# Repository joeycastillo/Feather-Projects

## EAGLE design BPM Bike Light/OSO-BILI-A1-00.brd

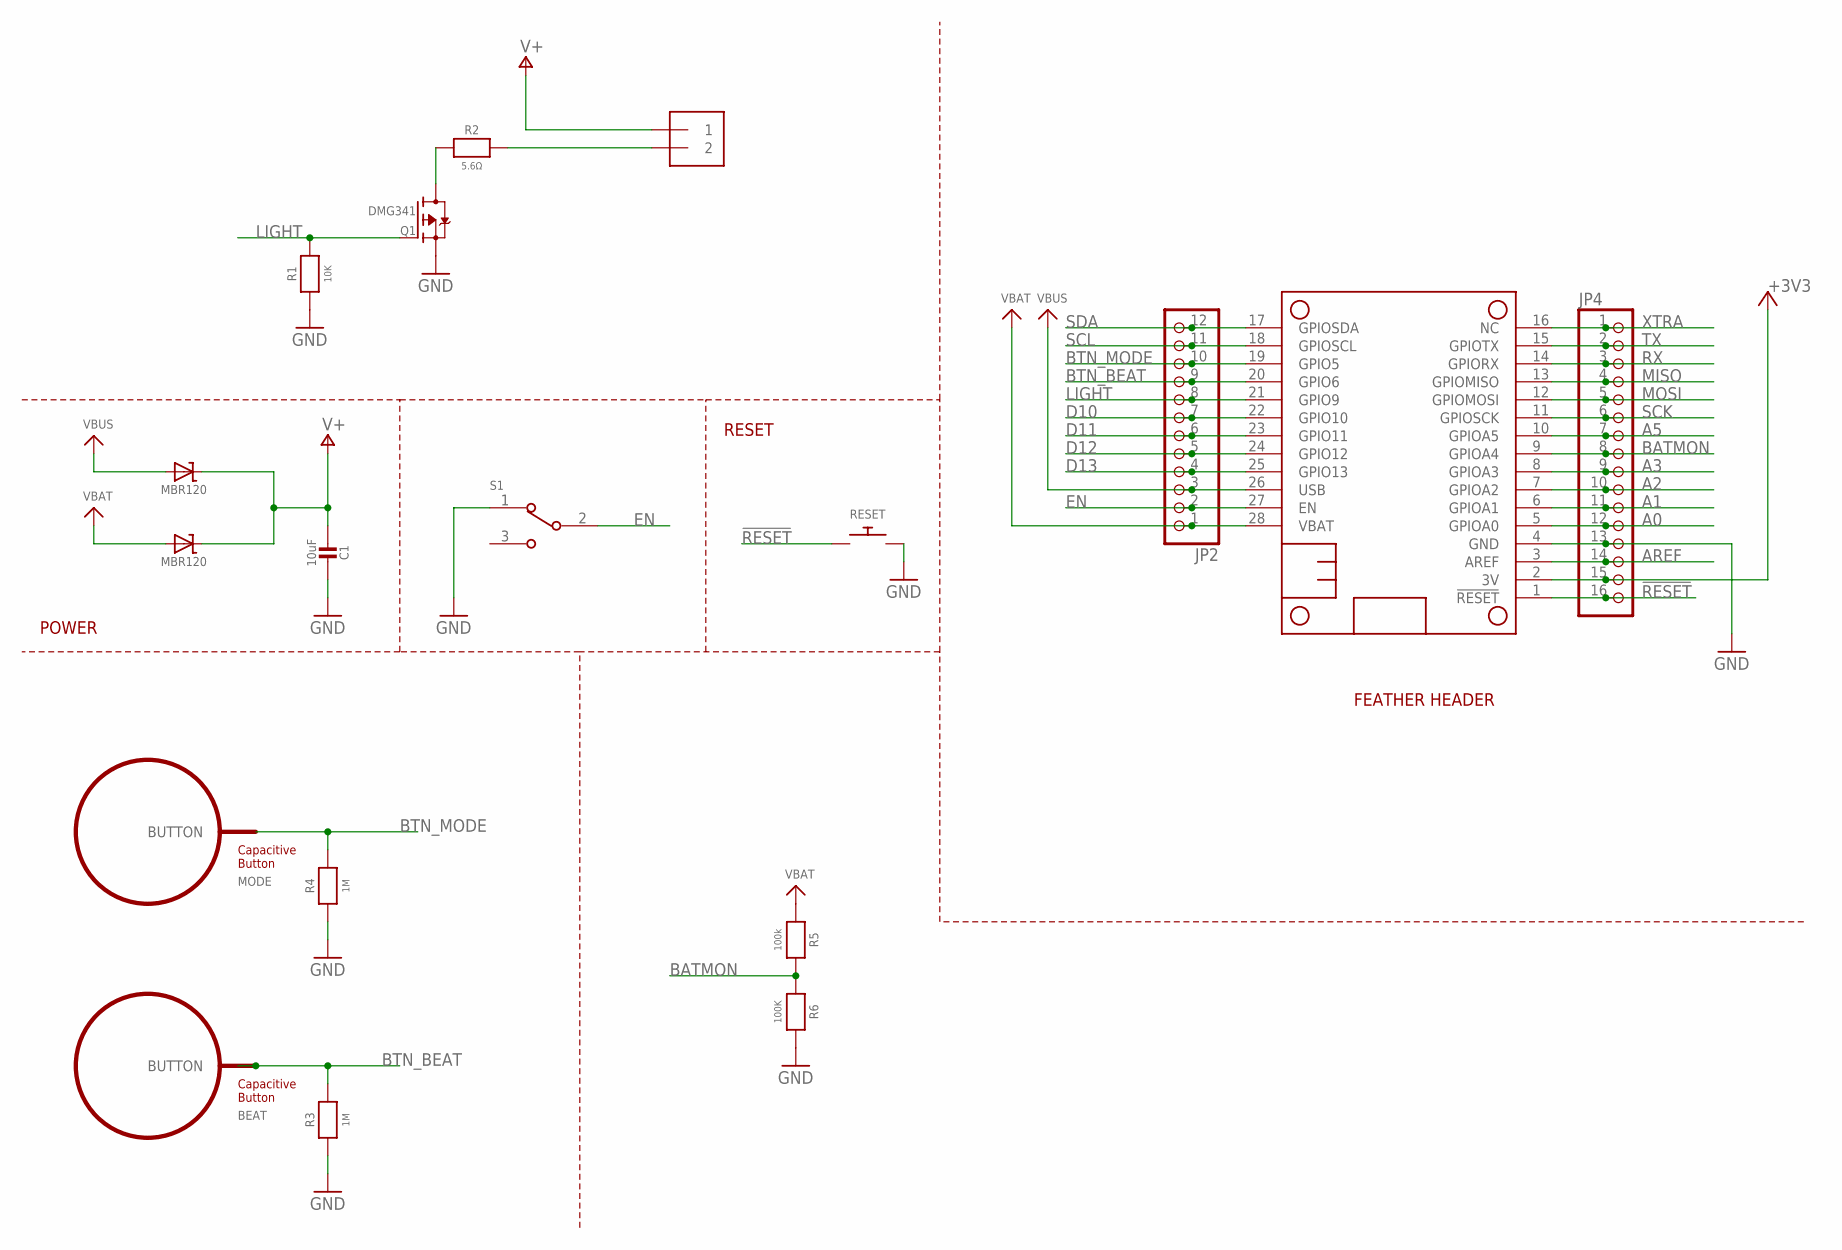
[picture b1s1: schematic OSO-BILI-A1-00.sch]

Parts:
BEAT: BUTTON_PASSIVE12MM; BUTTON_PASSIVE_12MM
C1: 10uF; 0805-NO
D1, D2: MBR120; SOD-123
J1: 1X25MM; 1X2-5MM
JP2: HEADER-1X12; 1X12_ROUND
JP4: HEADER-1X16ROUND; 1X16_ROUND
MODE: BUTTON_PASSIVE8MM; BUTTON_PASSIVE_8MM
MS1: FEATHERWING
Q1: DMG341; SOT23-R
R1: 10K; 0805-NO
R2: 5.6Ω; 2012
R3, R4: 1M; 0805-NO
R5: 100k; 0805_10MGAP
R6: 100K; 0805-NO
RESET: SWITCH_PUSHBUTTONC&K_KSS; BTN_CK_KSS
S1: JS102011SAQN; SW_JS102011SAQN

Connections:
3V: JP4.15, MS1.2 (3V)
!RESET: JP4.16, MS1.1 (!RESET), RESET.P$1
A0: JP4.12, MS1.5 (GPIOA0)
A1: JP4.11, MS1.6 (GPIOA1)
A2: JP4.10, MS1.7 (GPIOA2)
A3: JP4.9, MS1.8 (GPIOA3)
A5: JP4.7, MS1.10 (GPIOA5)
AREF: JP4.14, MS1.3 (AREF)
BATMON: JP4.8, MS1.9 (GPIOA4), R5.2, R6.1
BTN_BEAT: BEAT.BUTTON, JP2.9, MS1.20 (GPIO6), R3.2
BTN_MODE: JP2.10, MODE.BUTTON, MS1.19 (GPIO5), R4.2
D10: JP2.7, MS1.22 (GPIO10)
D11: JP2.6, MS1.23 (GPIO11)
D12: JP2.5, MS1.24 (GPIO12)
D13: JP2.4, MS1.25 (GPIO13)
EN: JP2.2, MS1.27 (EN), S1.2
GND: C1.1, JP4.13, MS1.4 (GND), Q1.2 (S), R1.1, R3.1, R4.1, R6.2, RESET.P$2, S1.1
LIGHT: JP2.8, MS1.21 (GPIO9), Q1.1 (G), R1.2
MISO: JP4.4, MS1.13 (GPIOMISO)
MOSI: JP4.5, MS1.12 (GPIOMOSI)
unnamed: Q1.3 (D), R2.1
unnamed: J1.2, R2.2
RX: JP4.3, MS1.14 (GPIORX)
SCK: JP4.6, MS1.11 (GPIOSCK)
SCL: JP2.11, MS1.18 (GPIOSCL)
SDA: JP2.12, MS1.17 (GPIOSDA)
TX: JP4.2, MS1.15 (GPIOTX)
V+: C1.2, D1.C, D2.C, J1.1
VBAT: D2.A, JP2.1, MS1.28 (VBAT), R5.1
VBUS: D1.A, JP2.3, MS1.26 (USB)
XTRA: JP4.1, MS1.16 (NC)

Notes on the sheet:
POWER
RESET
FEATHER HEADER

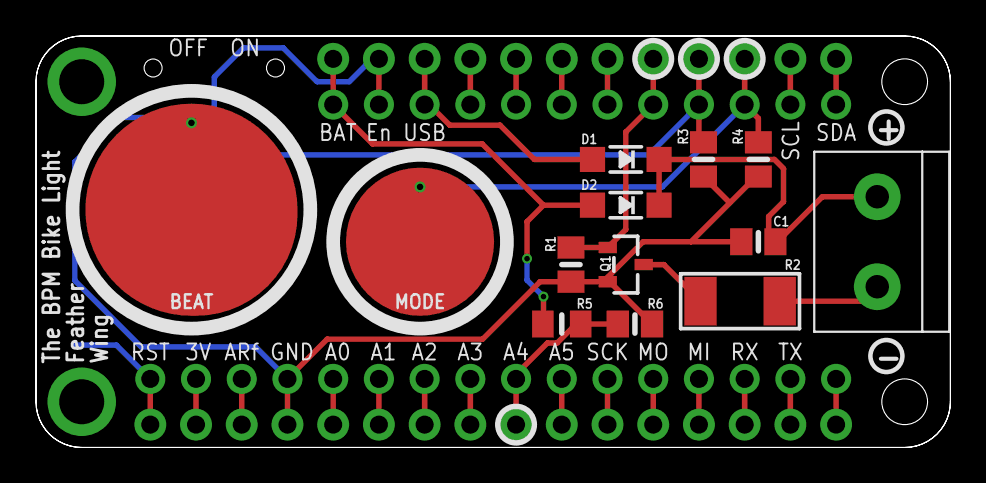
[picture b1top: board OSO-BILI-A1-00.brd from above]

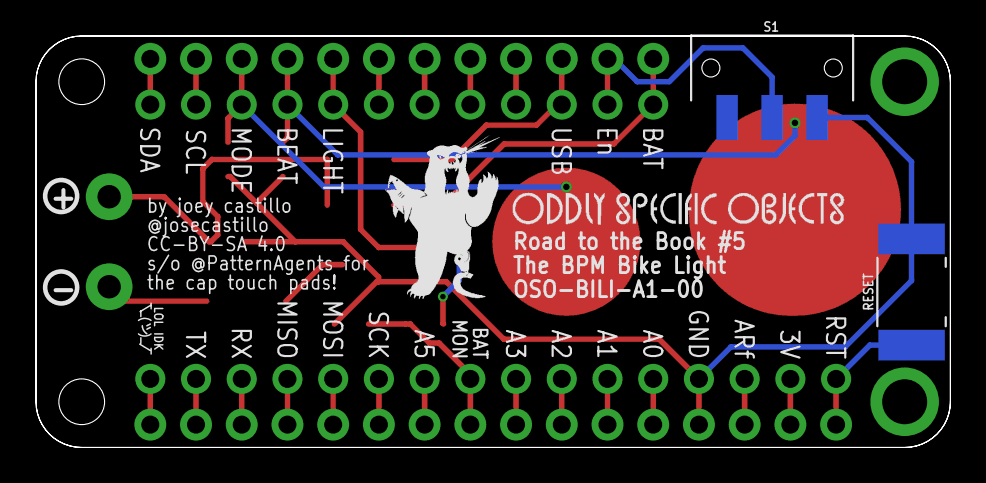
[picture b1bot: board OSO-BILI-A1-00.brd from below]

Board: 2 copper layers, 50.8 x 22.9 mm, 20 parts (4 on the bottom side), 31 nets.

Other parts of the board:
U$1: OSO_BEAR_250X360MIL_1000DPI
U$3: OSO_WORDMARK_ONELINE_725MIL_1000DPI

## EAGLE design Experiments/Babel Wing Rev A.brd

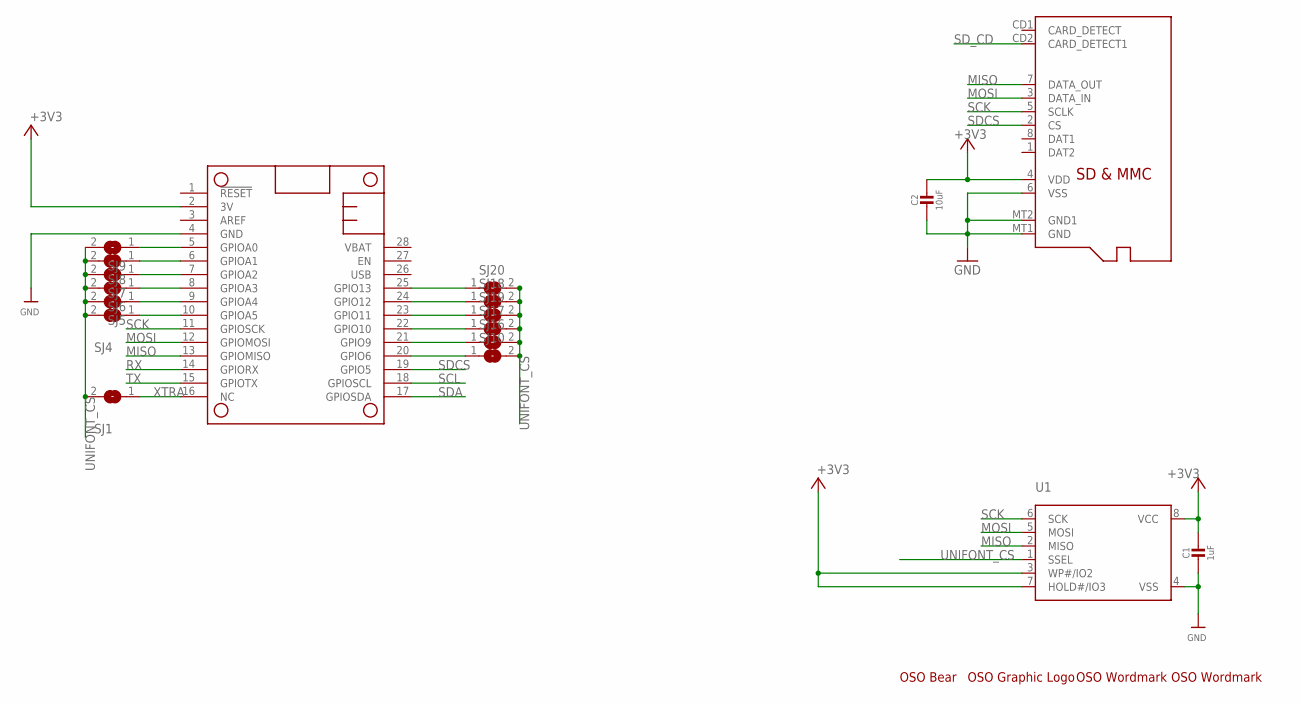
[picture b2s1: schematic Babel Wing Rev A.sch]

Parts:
C1: 1uF; 0805_10MGAP
C2: 10uF; 0805_10MGAP
MICROSD: MICROSD
MS1: FEATHERWING
SJ1, SJ4, SJ5, SJ6, SJ7, SJ8, SJ9, SJ10, SJ16, SJ17, SJ18, SJ19, SJ20: SOLDERJUMPER; SOLDERJUMPER_ARROW_NOPASTE
U1: MICROBUILDER_SPIFLASH_SOIC8; MICROBUILDER_SOIC8_150MIL
U$2: OSO_BEAR; OSO_BEAR_750MIL
U$3: OSO_GRAPHIC
U$4: OSO_TEXT; OSO_TEXT_435MIL
U$5: OSO_TEXTOSO_TEXT_ONELINE_125MIL; OSO_ONELINE_125MIL

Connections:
+3V3: C1.1, C2.1, MICROSD.4 (VDD), MS1.2 (3V), U1.3 (WP#/IO2), U1.7 (HOLD#/IO3), U1.8 (VCC)
GND: C1.2, C2.2, MICROSD.6 (VSS), MICROSD.MT1 (GND), MICROSD.MT2 (GND1), MS1.4 (GND), U1.4 (VSS)
MISO: MICROSD.7 (DATA_OUT), MS1.13 (GPIOMISO), U1.2 (MISO)
MOSI: MICROSD.3 (DATA_IN), MS1.12 (GPIOMOSI), U1.5 (MOSI)
unnamed: MS1.20 (GPIO6), SJ10.1
unnamed: MS1.10 (GPIOA5), SJ4.1
unnamed: MS1.9 (GPIOA4), SJ5.1
unnamed: MS1.8 (GPIOA3), SJ6.1
unnamed: MS1.7 (GPIOA2), SJ7.1
unnamed: MS1.6 (GPIOA1), SJ8.1
unnamed: MS1.5 (GPIOA0), SJ9.1
unnamed: MS1.25 (GPIO13), SJ20.1
unnamed: MS1.24 (GPIO12), SJ18.1
unnamed: MS1.23 (GPIO11), SJ19.1
unnamed: MS1.22 (GPIO10), SJ17.1
unnamed: MS1.21 (GPIO9), SJ16.1
RX: MS1.14 (GPIORX)
SCK: MICROSD.5 (SCLK), MS1.11 (GPIOSCK), U1.6 (SCK)
SCL: MS1.18 (GPIOSCL)
SDA: MS1.17 (GPIOSDA)
SDCS: MICROSD.2 (CS), MS1.19 (GPIO5)
SD_CD: MICROSD.CD2 (CARD_DETECT1)
TX: MS1.15 (GPIOTX)
UNIFONT_CS: SJ1.2, SJ4.2, SJ5.2, SJ6.2, SJ7.2, SJ8.2, SJ9.2, SJ10.2, SJ16.2, SJ17.2, SJ18.2, SJ19.2, SJ20.2, U1.1 (SSEL)
XTRA: MS1.16 (NC), SJ1.1

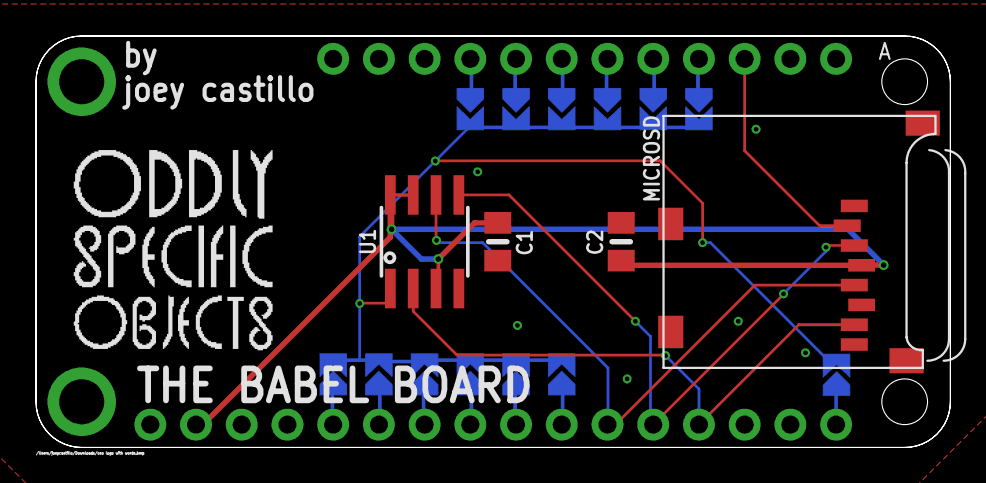
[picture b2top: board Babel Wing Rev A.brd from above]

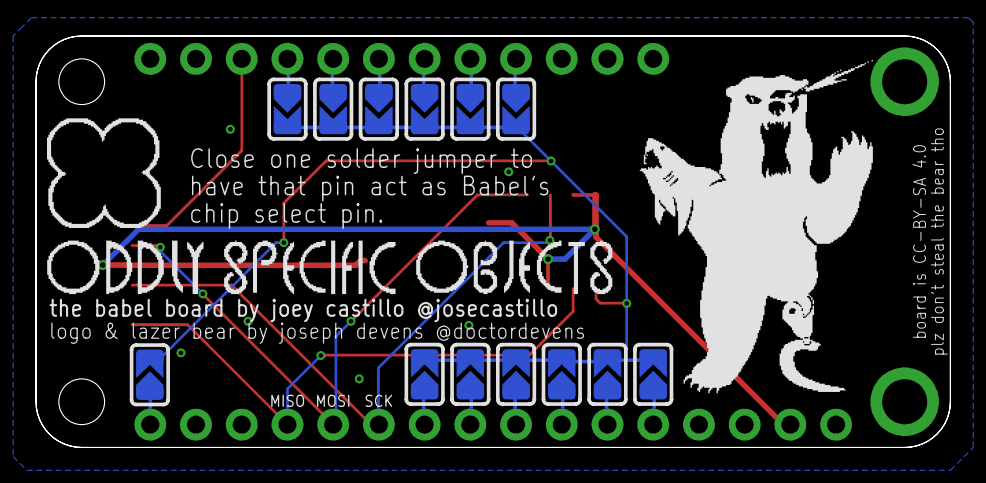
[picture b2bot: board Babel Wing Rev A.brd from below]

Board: 2 copper layers, 50.8 x 22.9 mm, 22 parts (16 on the bottom side), 20 nets.

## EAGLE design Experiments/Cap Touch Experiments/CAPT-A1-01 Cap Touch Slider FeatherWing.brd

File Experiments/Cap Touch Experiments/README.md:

# Capacitive Touch Experiments

Just some boards I made to play with the peripheral touch controller on the SAMD series boards. 

Slider design is based on a CC-licensed design from [Pattern Agents](http://www.patternagents.com/news/2013/11/29/touch-widgets-howto.html)

Matrix design kind of started from their passive matrix, but I expanded it and redid the symbol to work for my intended uses.

# Self-Capacitance Slider Wing

The slider wing should "just work" with [Adafruit FreeTouch](https://github.com/adafruit/Adafruit_FreeTouch) on the following boards:

* [Feather M0](https://www.adafruit.com/product/2772)
* [Feather M0 Express](https://www.adafruit.com/product/3403)
* [Feather M0 Adalogger](https://www.adafruit.com/product/2796)
* [Feather M0 Wifi](https://www.adafruit.com/product/3010)
* [Feather M0 Bluefruit LE](https://www.adafruit.com/product/2995)
* All the [LoRa](https://www.adafruit.com/product/3178) [and](https://www.adafruit.com/product/3179) [RadioFruit](https://www.adafruit.com/product/3176) [boards](https://www.adafruit.com/product/3177)

I'd love to get it working with the SAMD51-based [Feather M4 Express](https://www.adafruit.com/product/3857) but there's currently no open source support for the PTC on that board. If you want to hack on this, this slider might be an ideal testbed for that. (note that one of the segments is on a non-PTC line, so you would get a slightly shorter slider on the M4)

# Mutual Capacitance Matrix Shield

This board is kind of the opposite of "should just work". It's intended to work with the [Metro M0](https://www.adafruit.com/product/3505), but FreeTouch currently doesn't support mutual capacitance modes; I made this board so I could try hack on that. Also note that this shield kind of takes over almost all of your board's pins: it uses all of the analog pins and all but one of the digital pins, which isn't terribly convenient unless you're stacking with an SPI- or I2C-only shield.

If you're gonna try and play with this on a [Metro M4](https://www.adafruit.com/product/3382), that board lacks PTC functionality on pins A0 and A1, so I routed those pins to the top and bottom; this way, the matrix theoretically should work, just with a smaller touch area.

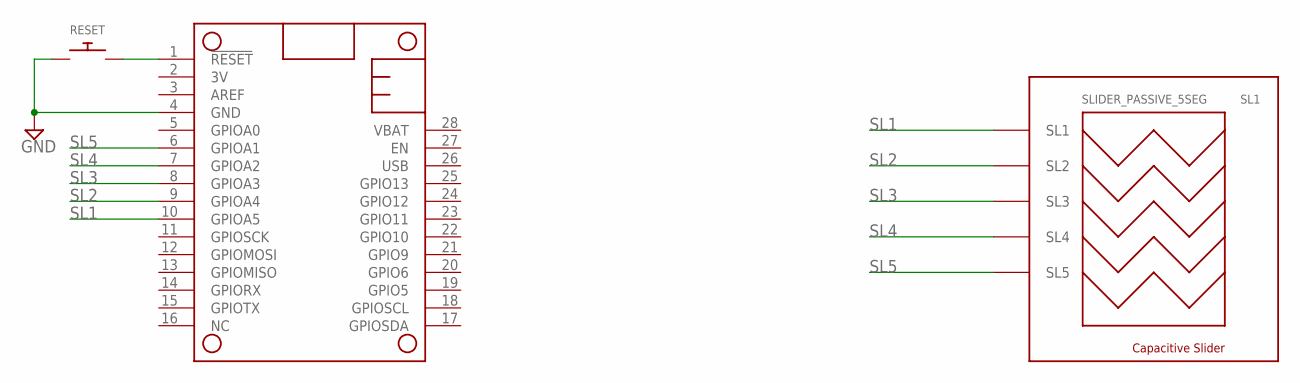
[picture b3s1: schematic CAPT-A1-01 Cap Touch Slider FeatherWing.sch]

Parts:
MS1: FEATHERWING
RESET: SPST_TACTILE_SWITCHRA-THRU; MJTP1117
SL1: SLIDER_PASSIVE_5SEG; SLIDER_PASSIVE_5SEG_12MM

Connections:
!RESET: MS1.1 (!RESET), RESET.P$2
GND: MS1.4 (GND), RESET.P$1
SL1: MS1.10 (GPIOA5), SL1.SL1
SL2: MS1.9 (GPIOA4), SL1.SL2
SL3: MS1.8 (GPIOA3), SL1.SL3
SL4: MS1.7 (GPIOA2), SL1.SL4
SL5: MS1.6 (GPIOA1), SL1.SL5

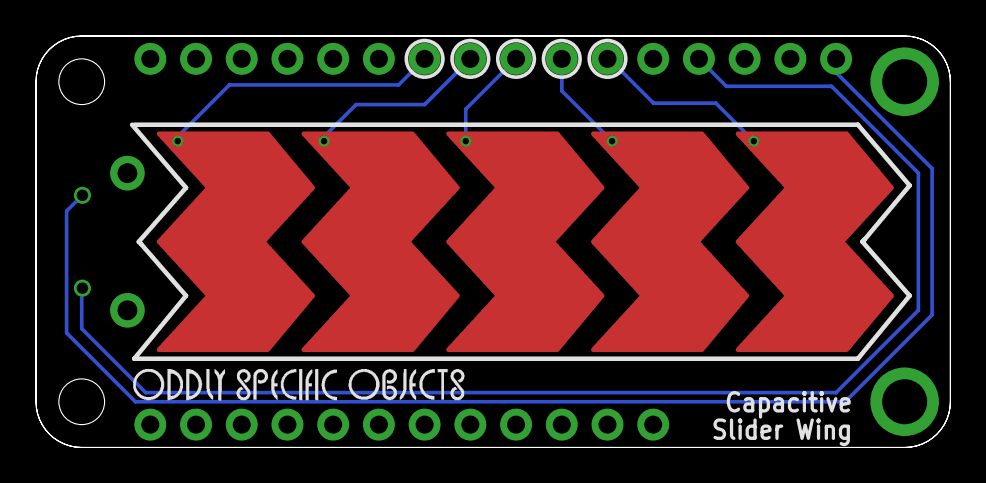
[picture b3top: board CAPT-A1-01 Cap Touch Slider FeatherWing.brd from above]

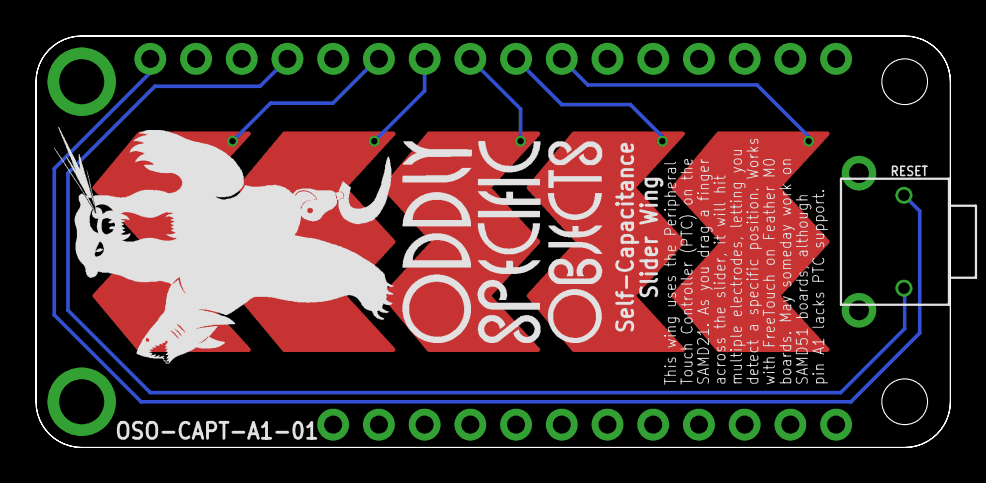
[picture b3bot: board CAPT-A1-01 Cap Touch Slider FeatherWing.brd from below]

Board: 2 copper layers, 50.8 x 22.9 mm, 6 parts (3 on the bottom side), 7 nets.

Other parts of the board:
U$1: OSO_WORDMARK_THREELINE_450MIL_1000DPI
U$2: OSO_BEAR_525X750MIL_1000DPI
U$3: OSO_WORDMARK_ONELINE_725MIL_1000DPI

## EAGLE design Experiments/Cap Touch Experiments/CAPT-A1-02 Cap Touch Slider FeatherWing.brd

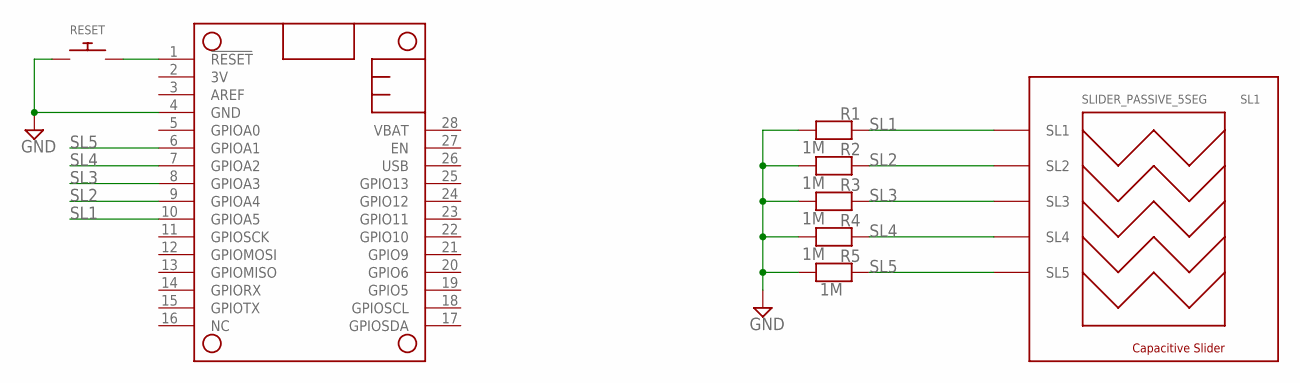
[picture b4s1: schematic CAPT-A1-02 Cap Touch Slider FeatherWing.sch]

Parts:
MS1: FEATHERWING
R1, R2, R3, R4, R5: 1M; 0805-NO
RESET: SPST_TACTILE_SWITCHRA-THRU; MJTP1117
SL1: SLIDER_PASSIVE_5SEG; SLIDER_PASSIVE_5SEG_12MM

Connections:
!RESET: MS1.1 (!RESET), RESET.P$2
GND: MS1.4 (GND), R1.2, R2.2, R3.2, R4.2, R5.2, RESET.P$1
SL1: MS1.10 (GPIOA5), R1.1, SL1.SL1
SL2: MS1.9 (GPIOA4), R2.1, SL1.SL2
SL3: MS1.8 (GPIOA3), R3.1, SL1.SL3
SL4: MS1.7 (GPIOA2), R4.1, SL1.SL4
SL5: MS1.6 (GPIOA1), R5.1, SL1.SL5

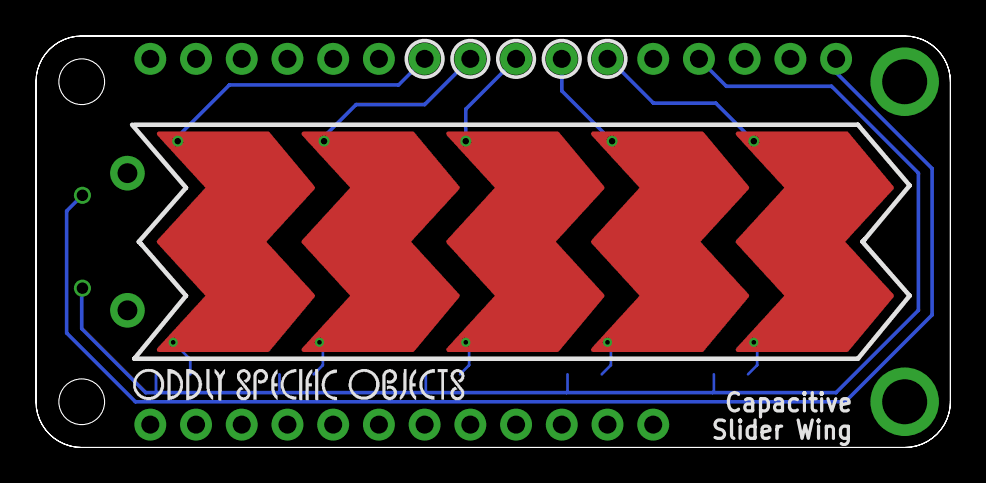
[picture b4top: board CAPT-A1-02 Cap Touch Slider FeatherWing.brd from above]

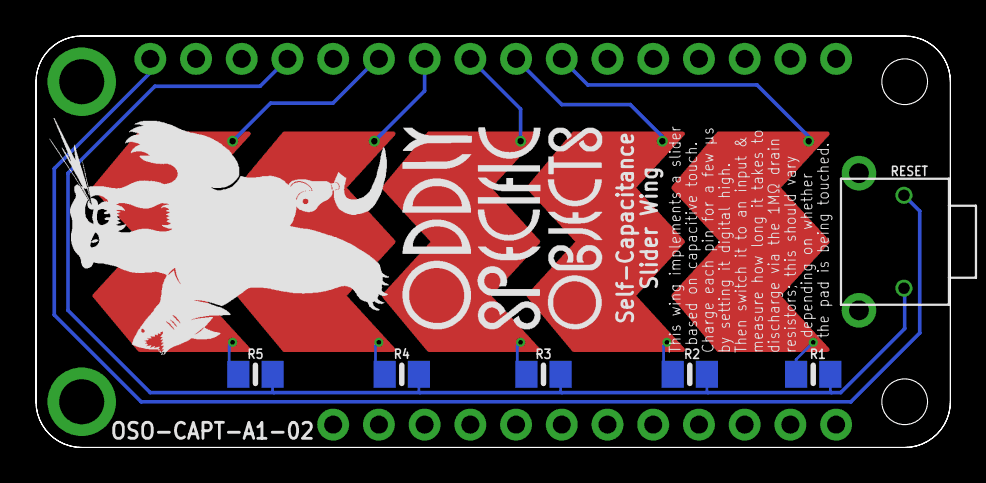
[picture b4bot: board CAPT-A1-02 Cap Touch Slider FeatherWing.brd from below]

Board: 2 copper layers, 50.8 x 22.9 mm, 11 parts (8 on the bottom side), 7 nets.

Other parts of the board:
U$1: OSO_WORDMARK_THREELINE_450MIL_1000DPI
U$2: OSO_BEAR_525X750MIL_1000DPI
U$3: OSO_WORDMARK_ONELINE_725MIL_1000DPI

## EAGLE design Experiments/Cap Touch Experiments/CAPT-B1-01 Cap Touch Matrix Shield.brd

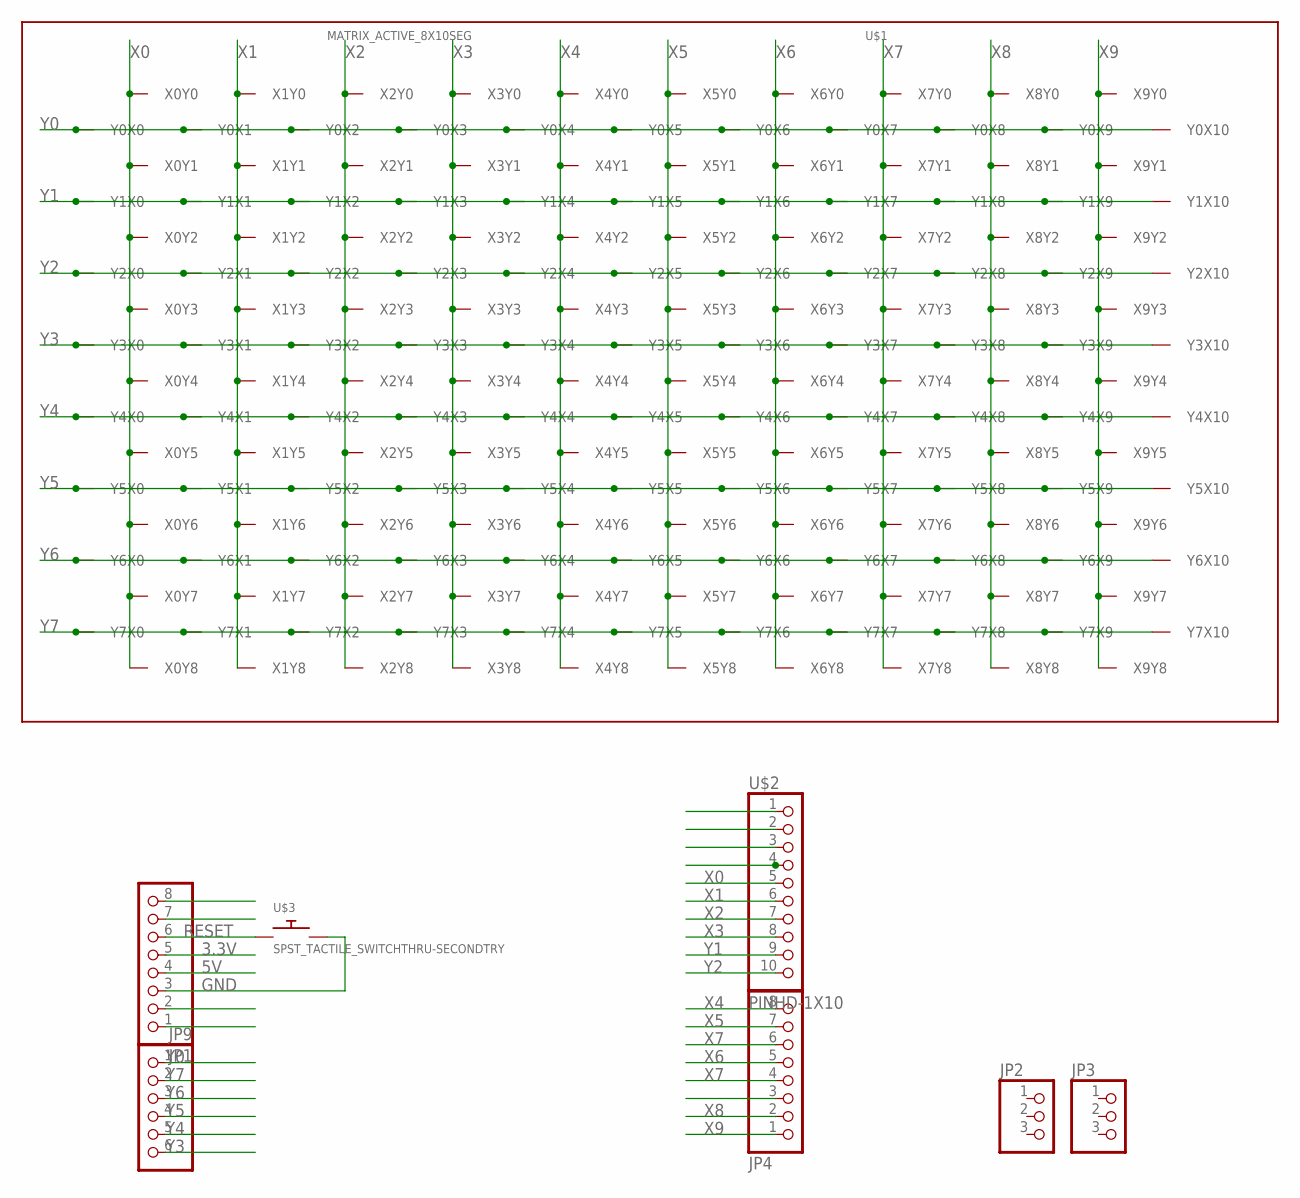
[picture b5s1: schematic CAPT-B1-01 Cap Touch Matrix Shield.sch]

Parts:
JP1, JP4: PINHD-1X8CLEANBIG; 1X08-CLEANBIG
JP2, JP3: PINHD-1X3CB; 1X03-CLEANBIG
JP9: PINHD-1X6CB; 1X06-CLEANBIG
U$1: MATRIX_ACTIVE_8X10SEG; MATRIX_ACTIVE_8X10SEG_4MM
U$2: PINHD-1X10; 1X10-BIG
U$3: SPST_TACTILE_SWITCHTHRU-SECONDTRY; MJTP1250-TRY2

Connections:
3.3V: JP1.5
5V: JP1.4
GND: JP1.3, U$3.P$2
RESET: JP1.6, U$3.P$1
X0: U$1.X0Y0, U$1.X0Y1, U$1.X0Y2, U$1.X0Y3, U$1.X0Y4, U$1.X0Y5, U$1.X0Y6, U$1.X0Y7, U$1.X0Y8, U$2.5
X1: U$1.X1Y0, U$1.X1Y1, U$1.X1Y2, U$1.X1Y3, U$1.X1Y4, U$1.X1Y5, U$1.X1Y6, U$1.X1Y7, U$1.X1Y8, U$2.6
X2: U$1.X2Y0, U$1.X2Y1, U$1.X2Y2, U$1.X2Y3, U$1.X2Y4, U$1.X2Y5, U$1.X2Y6, U$1.X2Y7, U$1.X2Y8, U$2.7
X3: U$1.X3Y0, U$1.X3Y1, U$1.X3Y2, U$1.X3Y3, U$1.X3Y4, U$1.X3Y5, U$1.X3Y6, U$1.X3Y7, U$1.X3Y8, U$2.8
X4: JP4.8, U$1.X4Y0, U$1.X4Y1, U$1.X4Y2, U$1.X4Y3, U$1.X4Y4, U$1.X4Y5, U$1.X4Y6, U$1.X4Y7, U$1.X4Y8
X5: JP4.7, U$1.X5Y0, U$1.X5Y1, U$1.X5Y2, U$1.X5Y3, U$1.X5Y4, U$1.X5Y5, U$1.X5Y6, U$1.X5Y7, U$1.X5Y8
X6: JP4.5, U$1.X6Y0, U$1.X6Y1, U$1.X6Y2, U$1.X6Y3, U$1.X6Y4, U$1.X6Y5, U$1.X6Y6, U$1.X6Y7, U$1.X6Y8
X7: JP4.4, JP4.6, U$1.X7Y0, U$1.X7Y1, U$1.X7Y2, U$1.X7Y3, U$1.X7Y4, U$1.X7Y5, U$1.X7Y6, U$1.X7Y7, U$1.X7Y8
X8: JP4.2, U$1.X8Y0, U$1.X8Y1, U$1.X8Y2, U$1.X8Y3, U$1.X8Y4, U$1.X8Y5, U$1.X8Y6, U$1.X8Y7, U$1.X8Y8
X9: JP4.1, U$1.X9Y0, U$1.X9Y1, U$1.X9Y2, U$1.X9Y3, U$1.X9Y4, U$1.X9Y5, U$1.X9Y6, U$1.X9Y7, U$1.X9Y8
Y0: JP9.1, U$1.Y0X0, U$1.Y0X1, U$1.Y0X2, U$1.Y0X3, U$1.Y0X4, U$1.Y0X5, U$1.Y0X6, U$1.Y0X7, U$1.Y0X8, U$1.Y0X9, U$1.Y0X10
Y1: U$1.Y1X0, U$1.Y1X1, U$1.Y1X2, U$1.Y1X3, U$1.Y1X4, U$1.Y1X5, U$1.Y1X6, U$1.Y1X7, U$1.Y1X8, U$1.Y1X9, U$1.Y1X10, U$2.9
Y2: U$1.Y2X0, U$1.Y2X1, U$1.Y2X2, U$1.Y2X3, U$1.Y2X4, U$1.Y2X5, U$1.Y2X6, U$1.Y2X7, U$1.Y2X8, U$1.Y2X9, U$1.Y2X10, U$2.10
Y3: JP9.6, U$1.Y3X0, U$1.Y3X1, U$1.Y3X2, U$1.Y3X3, U$1.Y3X4, U$1.Y3X5, U$1.Y3X6, U$1.Y3X7, U$1.Y3X8, U$1.Y3X9, U$1.Y3X10
Y4: JP9.5, U$1.Y4X0, U$1.Y4X1, U$1.Y4X2, U$1.Y4X3, U$1.Y4X4, U$1.Y4X5, U$1.Y4X6, U$1.Y4X7, U$1.Y4X8, U$1.Y4X9, U$1.Y4X10
Y5: JP9.4, U$1.Y5X0, U$1.Y5X1, U$1.Y5X2, U$1.Y5X3, U$1.Y5X4, U$1.Y5X5, U$1.Y5X6, U$1.Y5X7, U$1.Y5X8, U$1.Y5X9, U$1.Y5X10
Y6: JP9.3, U$1.Y6X0, U$1.Y6X1, U$1.Y6X2, U$1.Y6X3, U$1.Y6X4, U$1.Y6X5, U$1.Y6X6, U$1.Y6X7, U$1.Y6X8, U$1.Y6X9, U$1.Y6X10
Y7: JP9.2, U$1.Y7X0, U$1.Y7X1, U$1.Y7X2, U$1.Y7X3, U$1.Y7X4, U$1.Y7X5, U$1.Y7X6, U$1.Y7X7, U$1.Y7X8, U$1.Y7X9, U$1.Y7X10

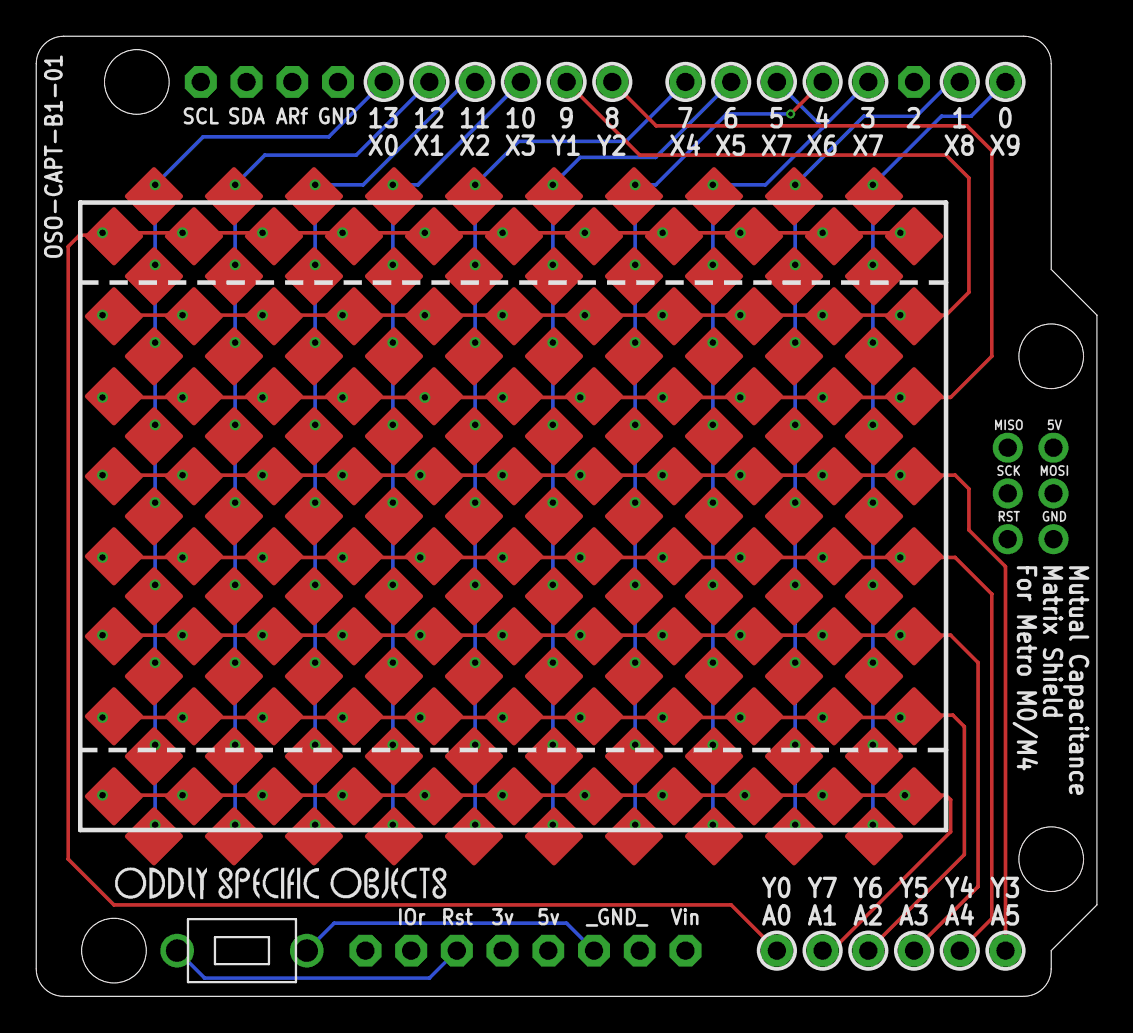
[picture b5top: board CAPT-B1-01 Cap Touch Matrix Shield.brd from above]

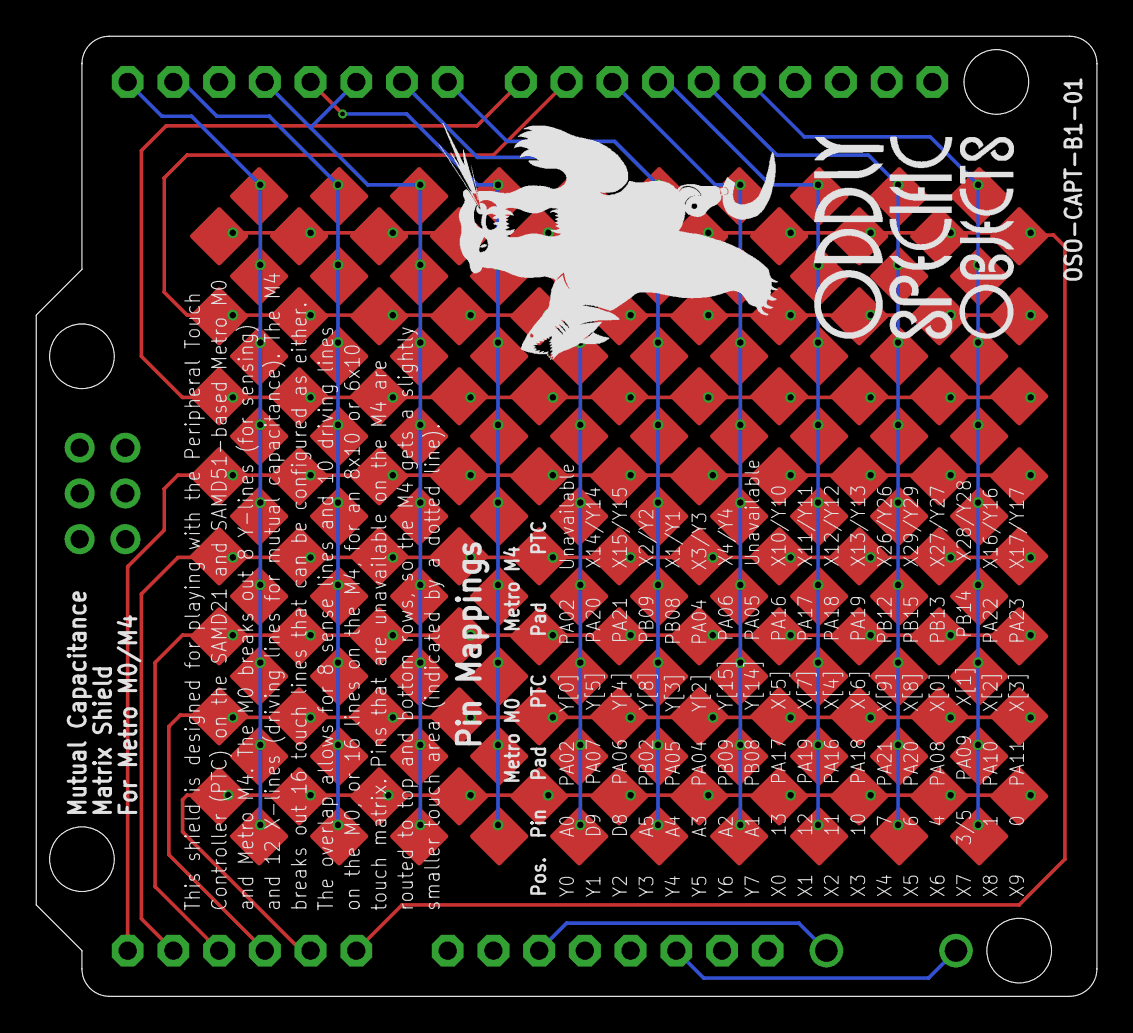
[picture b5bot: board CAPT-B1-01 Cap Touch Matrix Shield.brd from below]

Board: 2 copper layers, 58.9 x 53.3 mm, 11 parts (2 on the bottom side), 20 nets.

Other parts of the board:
U$4: OSO_BEAR_525X750MIL_1000DPI
U$5: OSO_WORDMARK_ONELINE_725MIL_1000DPI
U$6: OSO_WORDMARK_THREELINE_450MIL_1000DPI

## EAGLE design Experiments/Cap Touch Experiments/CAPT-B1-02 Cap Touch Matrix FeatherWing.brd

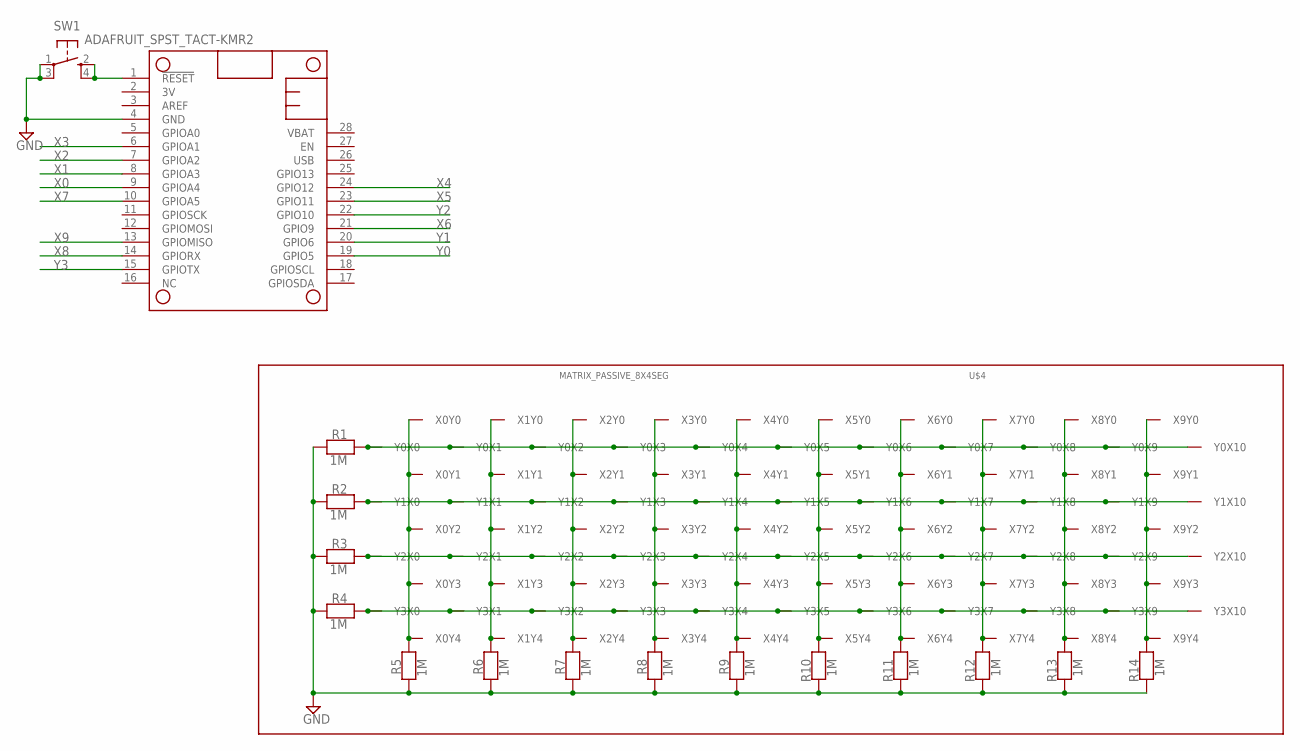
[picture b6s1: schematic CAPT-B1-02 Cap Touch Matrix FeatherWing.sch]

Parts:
MS2: MICROBUILDER_FEATHERWING_NOHOLES
R1, R2, R3, R4, R5, R6, R7, R8, R9, R10, R11, R12, R13, R14: 1M; 0805_10MGAP
SW1: ADAFRUIT_SPST_TACT-KMR2; ADAFRUIT_KMR2
U$4: MATRIX_PASSIVE_8X4SEG; MATRIX_ACTIVE_8X4SEG_4MM

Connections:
!RESET: MS2.1 (!RESET), SW1.2 (S), SW1.4 (S1)
GND: MS2.4 (GND), R1.2, R2.2, R3.2, R4.2, R5.2, R6.2, R7.2, R8.2, R9.2, R10.2, R11.2, R12.2, R13.2, R14.2, SW1.1, SW1.3 (P1)
X0: MS2.9 (GPIOA4), R5.1, U$4.X0Y0, U$4.X0Y1, U$4.X0Y2, U$4.X0Y3, U$4.X0Y4
X1: MS2.8 (GPIOA3), R6.1, U$4.X1Y0, U$4.X1Y1, U$4.X1Y2, U$4.X1Y3, U$4.X1Y4
X2: MS2.7 (GPIOA2), R7.1, U$4.X2Y0, U$4.X2Y1, U$4.X2Y2, U$4.X2Y3, U$4.X2Y4
X3: MS2.6 (GPIOA1), R8.1, U$4.X3Y0, U$4.X3Y1, U$4.X3Y2, U$4.X3Y3, U$4.X3Y4
X4: MS2.24 (GPIO12), R9.1, U$4.X4Y0, U$4.X4Y1, U$4.X4Y2, U$4.X4Y3, U$4.X4Y4
X5: MS2.23 (GPIO11), R10.1, U$4.X5Y0, U$4.X5Y1, U$4.X5Y2, U$4.X5Y3, U$4.X5Y4
X6: MS2.21 (GPIO9), R11.1, U$4.X6Y0, U$4.X6Y1, U$4.X6Y2, U$4.X6Y3, U$4.X6Y4
X7: MS2.10 (GPIOA5), R12.1, U$4.X7Y0, U$4.X7Y1, U$4.X7Y2, U$4.X7Y3, U$4.X7Y4
X8: MS2.14 (GPIORX), R13.1, U$4.X8Y0, U$4.X8Y1, U$4.X8Y2, U$4.X8Y3, U$4.X8Y4
X9: MS2.13 (GPIOMISO), R14.1, U$4.X9Y0, U$4.X9Y1, U$4.X9Y2, U$4.X9Y3, U$4.X9Y4
Y0: MS2.19 (GPIO5), R1.1, U$4.Y0X0, U$4.Y0X1, U$4.Y0X2, U$4.Y0X3, U$4.Y0X4, U$4.Y0X5, U$4.Y0X6, U$4.Y0X7, U$4.Y0X8, U$4.Y0X9, U$4.Y0X10
Y1: MS2.20 (GPIO6), R2.1, U$4.Y1X0, U$4.Y1X1, U$4.Y1X2, U$4.Y1X3, U$4.Y1X4, U$4.Y1X5, U$4.Y1X6, U$4.Y1X7, U$4.Y1X8, U$4.Y1X9, U$4.Y1X10
Y2: MS2.22 (GPIO10), R3.1, U$4.Y2X0, U$4.Y2X1, U$4.Y2X2, U$4.Y2X3, U$4.Y2X4, U$4.Y2X5, U$4.Y2X6, U$4.Y2X7, U$4.Y2X8, U$4.Y2X9, U$4.Y2X10
Y3: MS2.15 (GPIOTX), R4.1, U$4.Y3X0, U$4.Y3X1, U$4.Y3X2, U$4.Y3X3, U$4.Y3X4, U$4.Y3X5, U$4.Y3X6, U$4.Y3X7, U$4.Y3X8, U$4.Y3X9, U$4.Y3X10

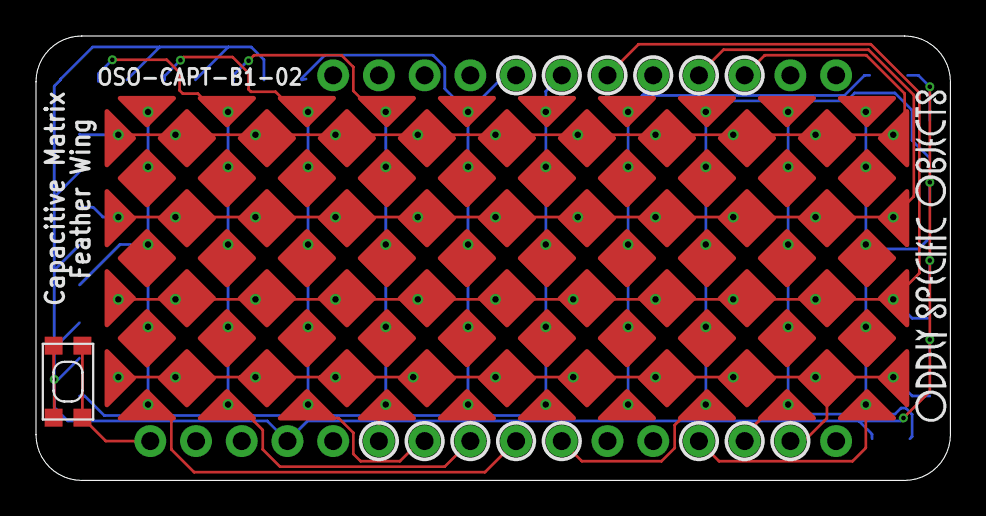
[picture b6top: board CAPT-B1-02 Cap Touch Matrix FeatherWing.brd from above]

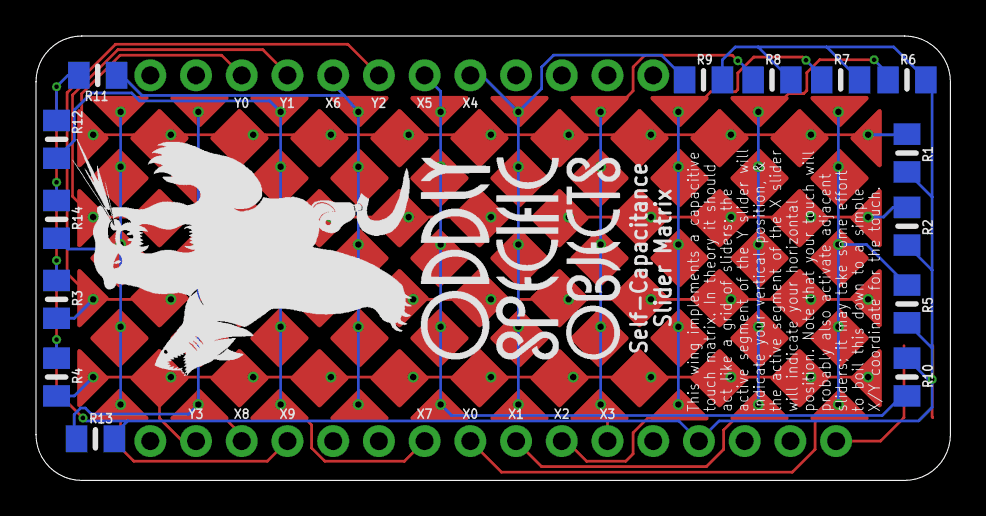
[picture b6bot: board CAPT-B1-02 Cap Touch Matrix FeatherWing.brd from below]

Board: 2 copper layers, 50.8 x 24.7 mm, 20 parts (16 on the bottom side), 16 nets.

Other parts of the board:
U$1: OSO_WORDMARK_THREELINE_450MIL_1000DPI
U$2: OSO_BEAR_525X750MIL_1000DPI
U$3: OSO_WORDMARK_ONELINE_725MIL_1000DPI

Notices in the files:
BPM Bike Light/OSO-BILI-A1-00.brd:
CC-BY-SA 4.0
Experiments/Babel Wing Rev A.brd:
board is CC-BY-SA 4.0
parts and their libraries:
microbuilder: This work is placed in the public domain, and may be freely used for commercial and non-commercial work with the following conditions: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
My Stuff: License : http://creativecommons.org/licenses/by-sa/3.1/ (Creative Commons 3.1)
